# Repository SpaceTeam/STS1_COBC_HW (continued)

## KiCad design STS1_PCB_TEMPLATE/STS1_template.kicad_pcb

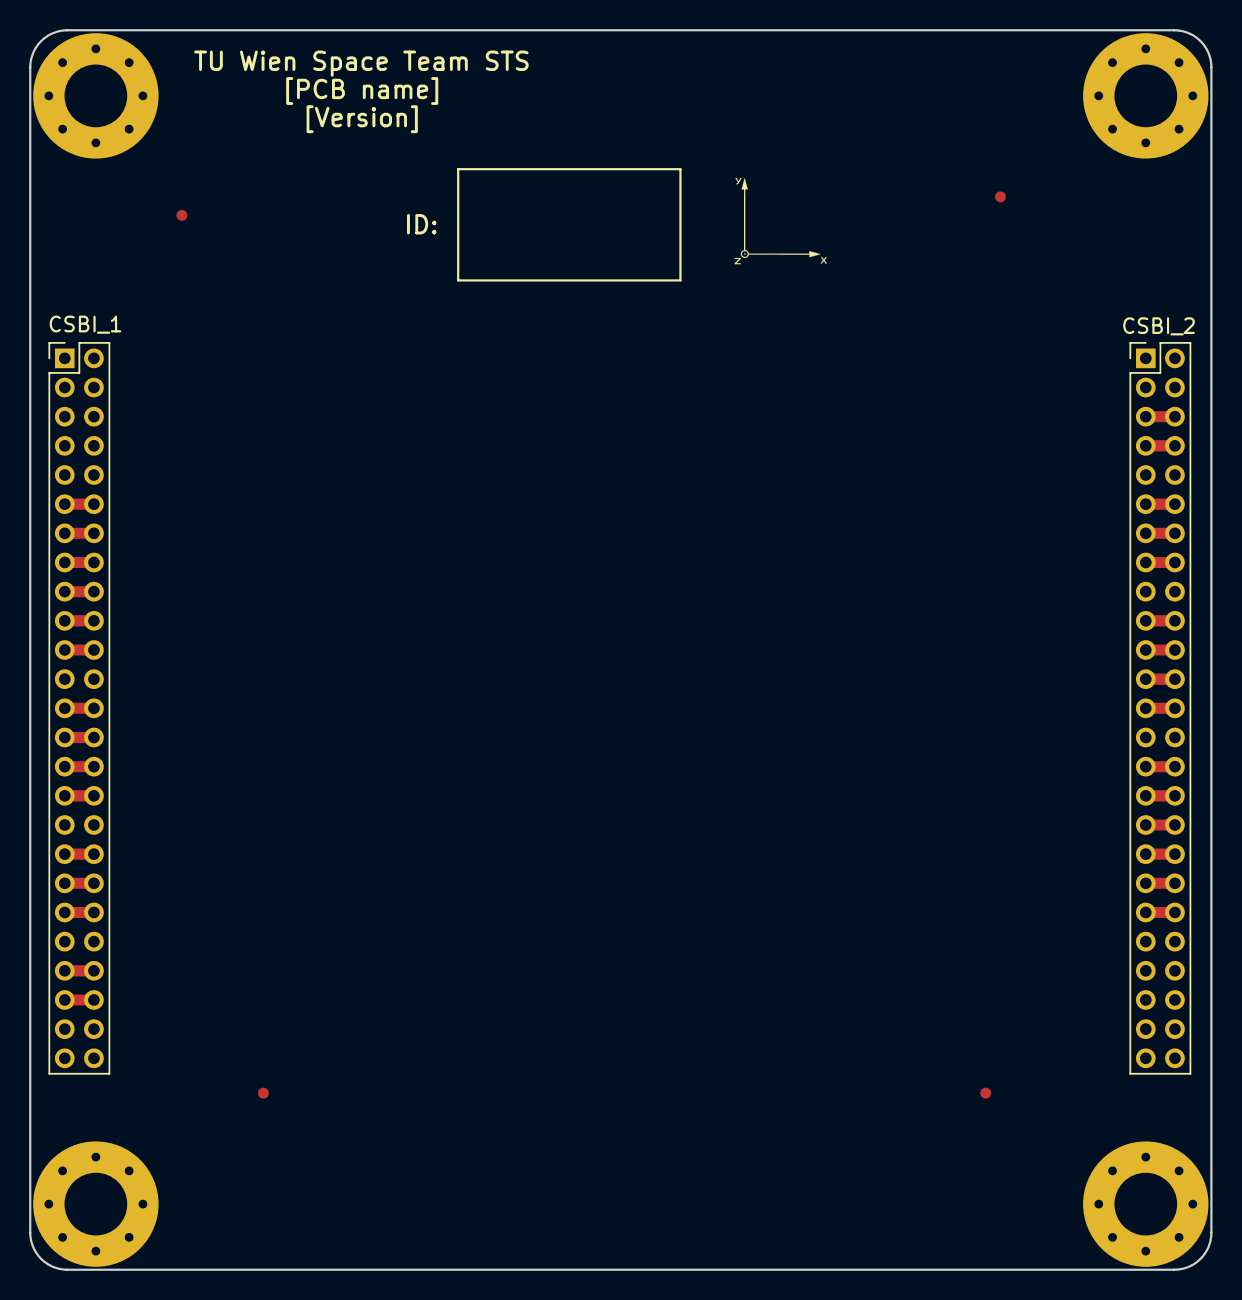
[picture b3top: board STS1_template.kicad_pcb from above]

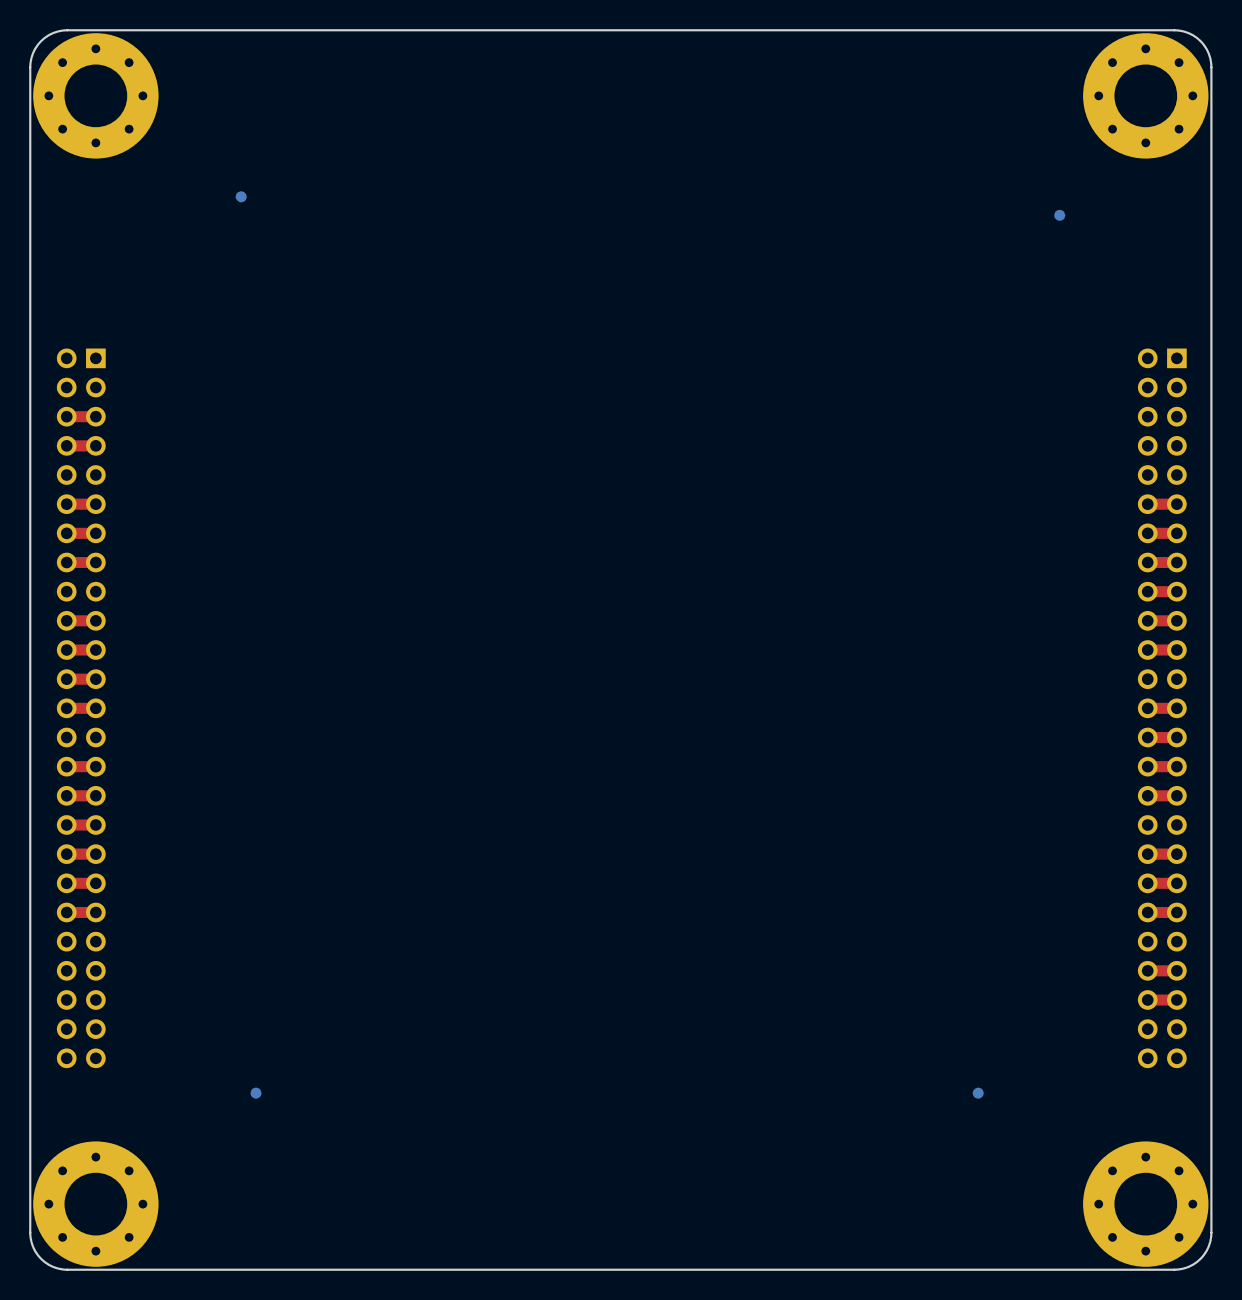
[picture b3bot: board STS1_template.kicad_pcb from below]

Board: 4 copper layers, 81.0 x 85.0 mm, 15 parts (4 on the bottom side), 32 nets.

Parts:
CSBI_1, CSBI_2: Conn_02x25_Odd_Even; PinHeader_2x25_P2.00mm_Vertical
FID1, FID2, FID3, FID4, FID5, FID6, FID7, FID8: Fiducial; Fiducial_0.75mm_Mask1.5mm
H1, H2, H3, H4: MountingHole_Pad; MountingHole_4.3mm_M4_Pad_Via
U1: coordinate_system; Coordinates

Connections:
/STS1_connector/COBC_SPI_1: CSBI_2.29, CSBI_2.30
/STS1_connector/COBC_SPI_2: CSBI_2.31, CSBI_2.32
/STS1_connector/COBC_SPI_3: CSBI_2.33, CSBI_2.34
/STS1_connector/COBC_SPI_4: CSBI_2.35, CSBI_2.36
/STS1_connector/COBC_SPI_5: CSBI_2.37, CSBI_2.38
/STS1_connector/COBC_SPI_6: CSBI_2.39, CSBI_2.40
/STS1_connector/EDU_BOOT: CSBI_2.15, CSBI_2.16
/STS1_connector/EDU_EN: CSBI_1.39, CSBI_1.40
/STS1_connector/EDU_Heartbeat: CSBI_1.35, CSBI_1.36
/STS1_connector/EDU_SPI_1: CSBI_1.21, CSBI_1.22
/STS1_connector/EDU_SPI_2: CSBI_1.19, CSBI_1.20
/STS1_connector/EDU_SPI_3: CSBI_1.17, CSBI_1.18
/STS1_connector/EDU_SPI_4: CSBI_1.15, CSBI_1.16
/STS1_connector/EDU_SPI_5: CSBI_1.13, CSBI_1.14
/STS1_connector/EDU_SPI_6: CSBI_1.11, CSBI_1.12
/STS1_connector/EDU_UPDATE: CSBI_1.37, CSBI_1.38
/STS1_connector/EPS_ANT_DEPLOYED: CSBI_2.23, CSBI_2.24
/STS1_connector/EPS_BAT_GOOD: CSBI_2.21, CSBI_2.22
/STS1_connector/EPS_CHARGING: CSBI_2.25, CSBI_2.26
/STS1_connector/UART_COBC_EDU_1: CSBI_1.45, CSBI_1.46
/STS1_connector/UART_COBC_EDU_2: CSBI_1.43, CSBI_1.44
/STS1_connector/UCI_COBC_3V3: CSBI_2.19, CSBI_2.20
/STS1_connector/UCI_COBC_UART_1: CSBI_2.5, CSBI_2.6
/STS1_connector/UCI_COBC_UART_2: CSBI_2.7, CSBI_2.8
GND: CSBI_1.1, CSBI_1.2, CSBI_1.3, CSBI_1.4, CSBI_1.9, CSBI_1.10, CSBI_1.23, CSBI_1.24, CSBI_1.33, CSBI_1.34, CSBI_1.41, CSBI_1.42, CSBI_1.47, CSBI_1.48, CSBI_1.49, CSBI_1.50, CSBI_2.1, CSBI_2.2, CSBI_2.3, CSBI_2.4, CSBI_2.9, CSBI_2.10, CSBI_2.17, CSBI_2.18, CSBI_2.27, CSBI_2.28, CSBI_2.41, CSBI_2.42, CSBI_2.47, CSBI_2.48, CSBI_2.49, CSBI_2.50, H1.1, H2.1, H3.1, H4.1
unnamed: CSBI_1.25, CSBI_1.26
unnamed: CSBI_1.27, CSBI_1.28
unnamed: CSBI_1.29, CSBI_1.30
unnamed: CSBI_1.31, CSBI_1.32
unnamed: CSBI_2.11, CSBI_2.12
unnamed: CSBI_2.13, CSBI_2.14
VBUS: CSBI_1.5, CSBI_1.6, CSBI_1.7, CSBI_1.8, CSBI_2.43, CSBI_2.44, CSBI_2.45, CSBI_2.46

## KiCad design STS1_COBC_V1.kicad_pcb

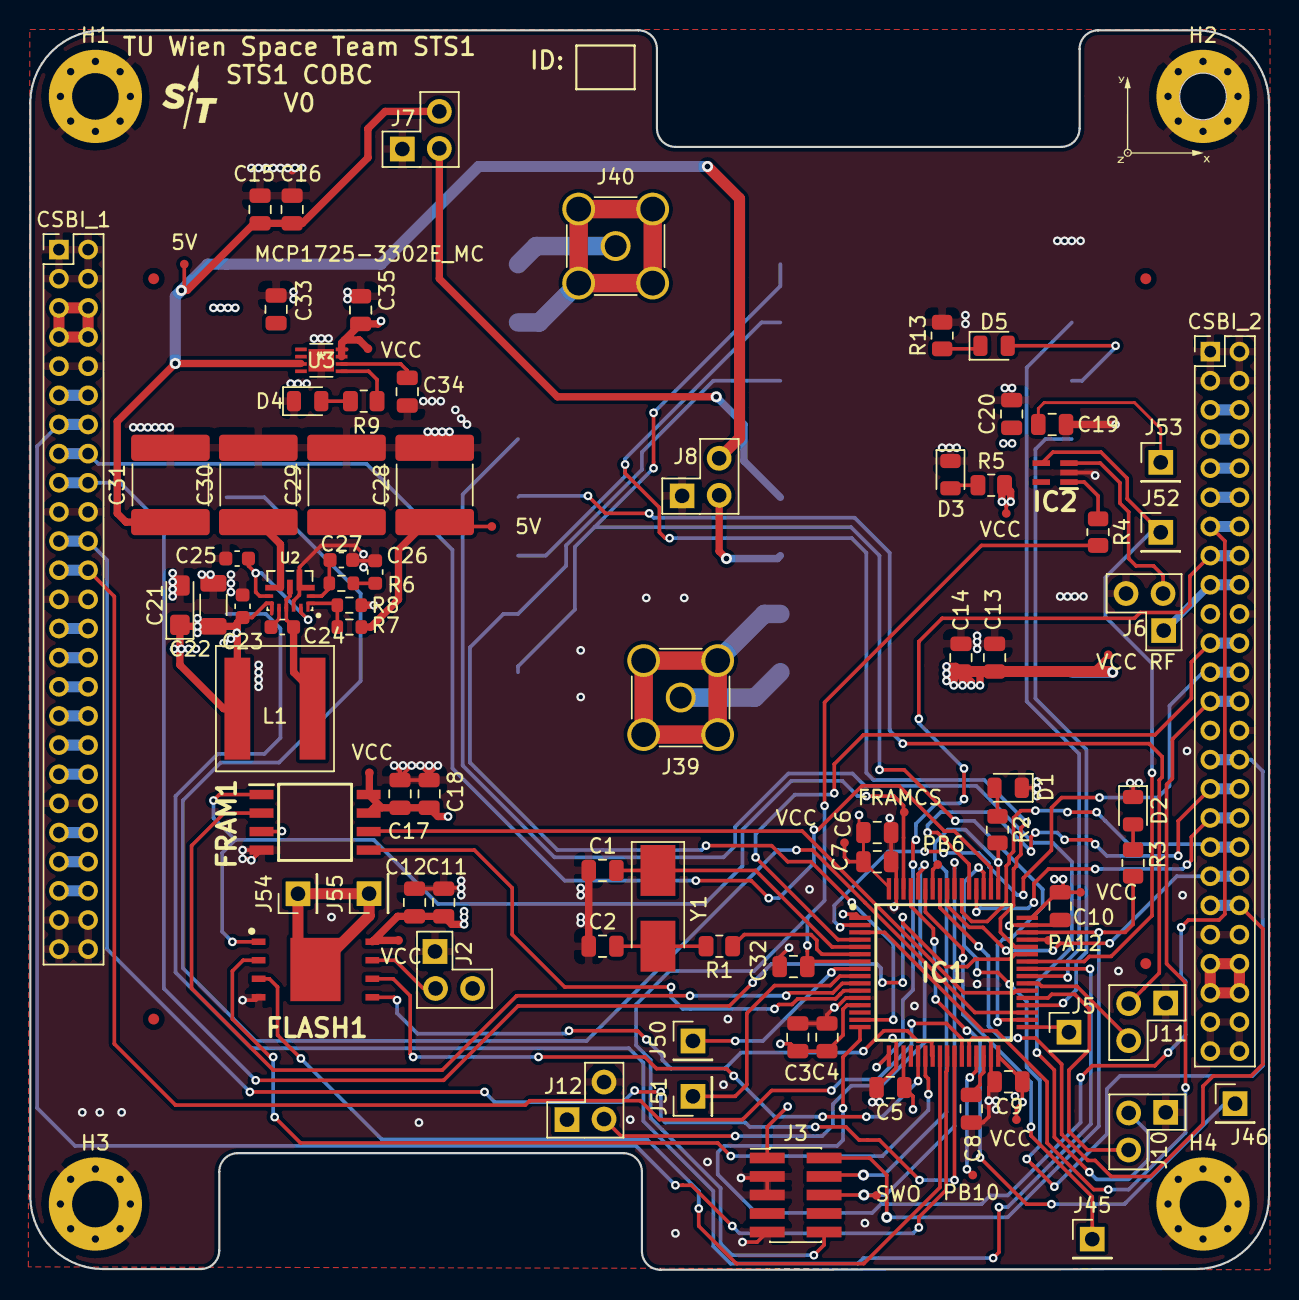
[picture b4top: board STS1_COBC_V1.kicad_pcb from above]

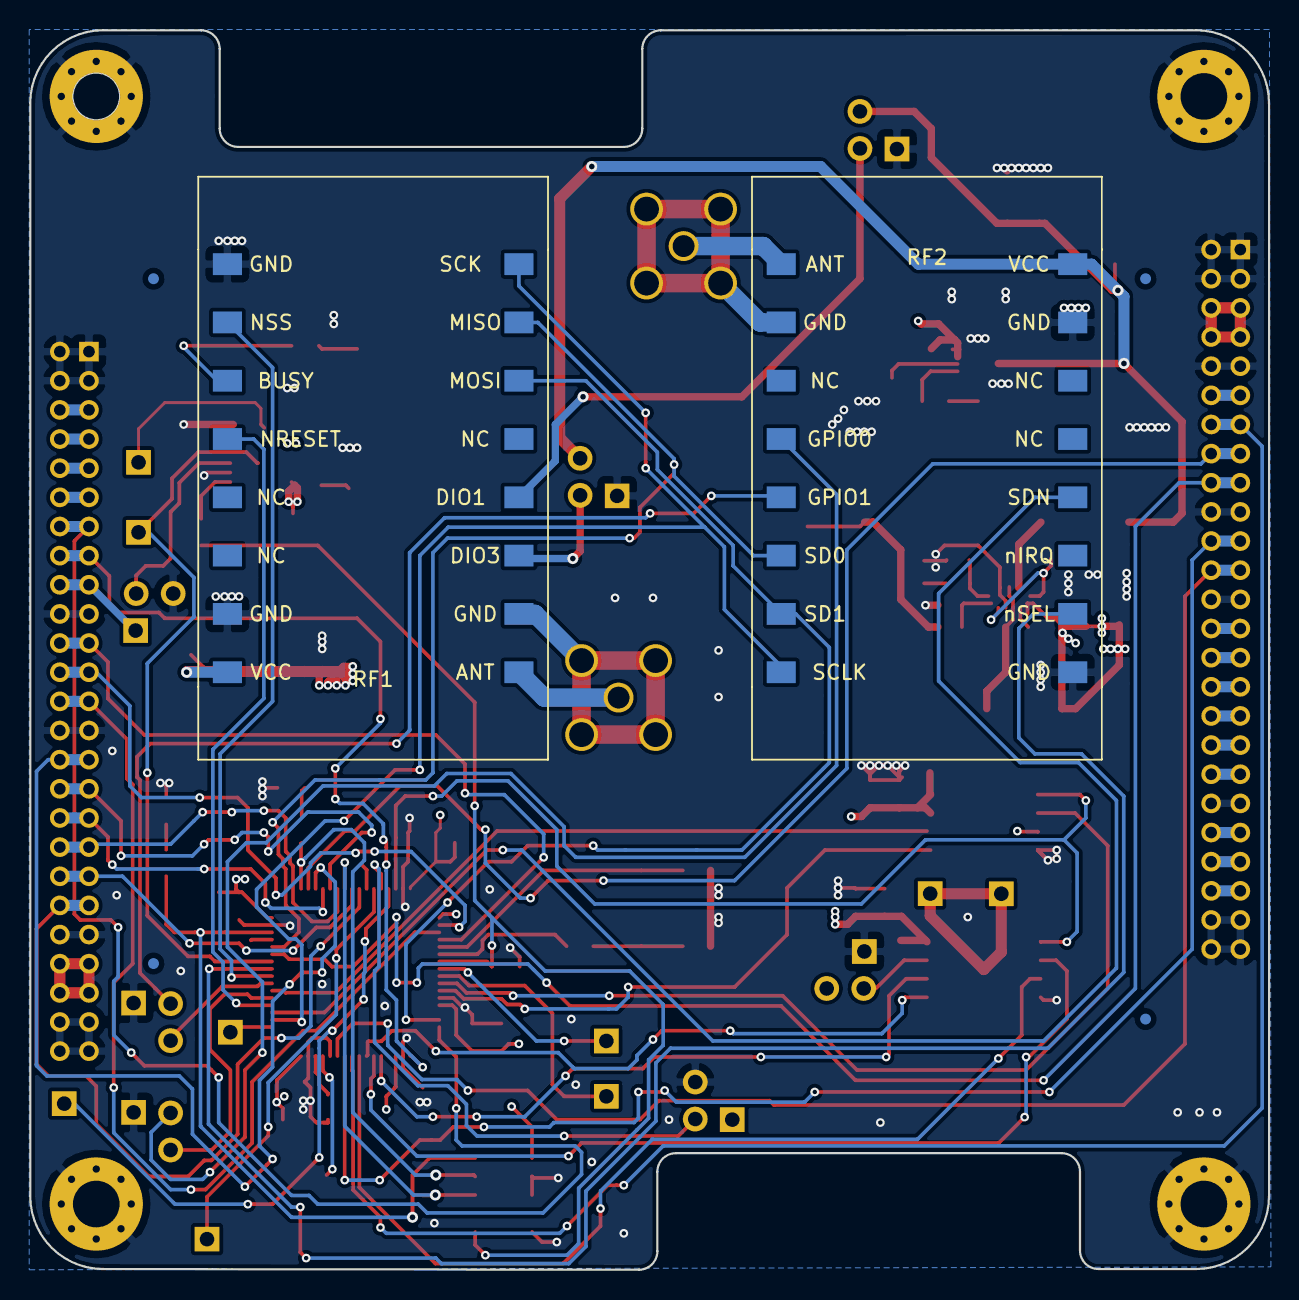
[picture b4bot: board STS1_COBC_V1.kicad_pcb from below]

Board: 4 copper layers, 85.0 x 85.0 mm, 109 parts (6 on the bottom side), 95 nets.

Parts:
5V, 5V#2: TestPoint; STS1_Testpoint
C1, C2: 20p; C_0805_2012Metric
C3: 1u; C_0805_2012Metric
C4, C5, C7, C9, C10, C11, C13, C15, C17, C19, C32: 100n; C_0805_2012Metric
C6, C8: 4.7u; C_0805_2012Metric
C12, C14, C16, C18, C20: 47u; C_0805_2012Metric
C21: 47uF; CP_EIA-3216-18_Kemet-A
C22: 10uF; C_1206_3216Metric
C23: 100nF; C_0603_1608Metric
C24: 150nF; C_0603_1608Metric
C25: 2.2uF; C_0603_1608Metric
C26: 39nF; C_0603_1608Metric
C27: 82pF; C_0603_1608Metric
C28, C29, C30, C31: 68uF; C_2220_5650Metric
C33, C35: 4.7µF; C_0805_2012Metric
C34: 0.1µ; C_0805_2012Metric
CSBI_1, CSBI_2: Conn_02x25_Odd_Even; PinHeader_2x25_P2.00mm_Vertical
D1, D2, D3, D4, D5: LED; LED_0805_2012Metric
FID1, FID2, FID3, FID4, FID5, FID6, FID7, FID8: Fiducial; Fiducial_0.75mm_Mask1.5mm
FLASH1: W25Q01JVZEIQ; SON127P800X600X80-9N-D
FRAM1: CY15B108QN-40SXI; SOIC127P800X203-8N
FRAMCS: TestPoint; STS1_Testpoint
H1, H2, H3, H4: MountingHole_Pad; MountingHole_3.2mm_M3_Pad_Via
IC1: STM32F411RET6TR; QFP50P1200X1200X160-64N
IC2: STWD100PYW83F; SOT65P210X110-5N
J2, J6, J7, J8, J10, J11, J12: Conn_01x03_Male; PinHeader_1x03_P2.54mm_Vertical_umdieEcke
J3: Conn_ARM_JTAG_SWD_10; PinHeader_2x05_P1.27mm_Vertical_SMD
J5, J45, J46, J50, J51, J52, J53, J54: Conn_01x01_Male; PinHeader_1x01_P2.54mm_Vertical
J39, J40: Conn_Coaxial; SMA_Amphenol_901-144_Vertical
J55: Conn_01x01_Female; PinHeader_1x01_P2.54mm_Vertical
L1: 1uH; XAL8080
PA12: TestPoint; STS1_Testpoint
PB6, PB10: TestPoint; STS1_Testpoint
R1: 220; R_0805_2012Metric
R2, R3, R5: 100; R_0805_2012Metric
R4: 4k7; R_0805_2012Metric
R6, R8: 48k7; R_0603_1608Metric
R7: 357k; R_0603_1608Metric
R9: 1k; R_0805_2012Metric
R13: 15; R_0805_2012Metric
RF1: LoRa1268F30
RF2: RF4463F30; STS1_RF4463F30
SWO: TestPoint; STS1_Testpoint
U1: coordinate_system; Coordinates
U2: TPS61288; VQFN-HR
U3: MCP1725-3302E_MC; MCP1725-3302E&slash_MC
VCC: TestPoint; STS1_Testpoint
VCC RF: TestPoint; STS1_Testpoint
VCC#2, VCC#3, VCC#4, VCC#5, VCC#6, VCC#7: TestPoint; STS1_Testpoint
Y1: 12MHz; Crystal_SMD_5032-2Pin_5.0x3.2mm_HandSoldering

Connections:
+3V3: C3.1, C4.2, C5.2, C6.2, C7.2, C9.1, C10.1, C11.2, C12.2, C17.2, C18.2, C19.1, C20.1, C35.2, CSBI_2.17, CSBI_2.18, FLASH1.8, FRAM1.3, FRAM1.7, FRAM1.8, IC1.1, IC1.13, IC1.19, IC1.32, IC1.48, IC1.64, IC2.5, J2.3, J3.1, J6.1, J12.1, J53.1, R5.2, U3.7, U3.8, VCC.1, VCC#2.1, VCC#3.1, VCC#4.1, VCC#5.1, VCC#6.1, VCC#7.1
+5V: 5V.1, 5V#2.1, C13.1, C14.1, C15.1, C16.1, C28.1, C29.1, C30.1, C31.1, C33.2, J7.3, J8.3, R7.1, RF1.1, RF2.1, U2.5, U3.1, U3.2, U3.3, VCC RF.1
/COBC_SPI_1: CSBI_2.29, CSBI_2.30, IC1.51
/COBC_SPI_2: CSBI_2.31, CSBI_2.32, IC1.53
/COBC_SPI_3: CSBI_2.33, CSBI_2.34, IC1.52
/COBC_SPI_4: CSBI_2.35, CSBI_2.36, IC1.54
/COBC_SPI_5: CSBI_2.37, CSBI_2.38, IC1.56
/COBC_SPI_6: CSBI_2.39, CSBI_2.40, IC1.57
/EDU_EN: CSBI_1.21, CSBI_1.22, IC1.26
/EDU_Heartbeat: CSBI_1.13, CSBI_1.14, IC1.25
/EDU_UPDATE: CSBI_1.23, CSBI_1.24, IC1.27
/EPS_ANT_DEP: CSBI_2.23, CSBI_2.24, IC1.2
/EPS_BAT_GOOD: CSBI_2.21, CSBI_2.22, IC1.4
/EPS_CHARGING: CSBI_2.25, CSBI_2.26, IC1.3
/LoRa_NRESET: IC1.36, RF1.5
/RF4463F30_GPIO0: IC1.37, J10.3
/RF4463F30_GPIO1: IC1.39, J11.3
/RF4463F30_SDN: IC1.35, RF2.5
/STS1_COBC_Memories/FRAM_CLK: FRAM1.6, IC1.38
/STS1_COBC_Memories/FRAM_CS: FLASH1.1, FRAM1.1, FRAMCS.1, IC1.62
/STS1_COBC_Memories/FRAM_DataInput: FRAM1.5, IC1.11
/STS1_COBC_Memories/FRAM_DataOutput: FRAM1.2, IC1.10
/STS1_COBC_Memories/Flash_CLK: FLASH1.6, IC1.21
/STS1_COBC_Memories/Flash_DataInput: FLASH1.5, IC1.23
/STS1_COBC_Memories/Flash_DataOutput: FLASH1.2, IC1.22
/STS1_COBC_Memories/Flash_WP: FLASH1.3, IC1.24
/STS1_COBC_uC/PB6: IC1.58, PB6.1
/STS1_COBC_uC/PB7: IC1.59, J45.1
/STS1_COBC_uC/PB9: IC1.61, J46.1
/STS1_COBC_uC/PC0: IC1.8, J50.1
/STS1_COBC_uC/PC1: IC1.9, J51.1
/STS1_COBC_uC/SPI4_NSS: IC1.33, J5.1
/STS1_COBC_uC/STM32_NRST: C32.2, IC1.7, J3.10, R4.2
/STS1_COBC_uC/SWDCLK: IC1.49, J3.4, R2.2
/STS1_COBC_uC/SWDIO: IC1.46, J3.2, R3.2
/STS1_COBC_uC/SWO: IC1.55, J3.6, SWO.1
/STS1_COBC_uC/WDT_Clear: IC1.42, IC2.4, J52.1
/STS1_Connector/EDU_SPI_1: CSBI_1.27, CSBI_1.28
/STS1_Connector/EDU_SPI_2: CSBI_1.29, CSBI_1.30
/STS1_Connector/EDU_SPI_3: CSBI_1.31, CSBI_1.32
/STS1_Connector/EDU_SPI_4: CSBI_1.33, CSBI_1.34
/STS1_Connector/EDU_SPI_5: CSBI_1.35, CSBI_1.36
/STS1_Connector/EDU_SPI_6: CSBI_1.37, CSBI_1.38
/STS1_RF/LoRa_MISO: IC1.44, RF1.10, RF2.11
/STS1_RF/LoRa_MOSI: IC1.15, RF1.11, RF2.10
/STS1_RF/LoRa_NSS: IC1.40, RF1.7
/STS1_RF/LoRa_SMA_GND: J39.2, RF1.15
/STS1_RF/LoRa_SPI_CLK: IC1.34, RF1.9, RF2.9
/STS1_RF/RF4463_ANT_GND: J40.2, RF2.15
/STS1_RF/RF4463_nSEL: IC1.41, RF2.7
/UART_COBC_EDU_1: CSBI_1.15, CSBI_1.16, IC1.50
/UART_COBC_EDU_2: CSBI_1.17, CSBI_1.18, IC1.43
/UCI_COBC_UART_1: CSBI_2.13, CSBI_2.14, IC1.16
/UCI_COBC_UART_2: CSBI_2.15, CSBI_2.16, IC1.17
GND: C1.1, C2.1, C3.2, C4.1, C5.1, C6.1, C7.1, C8.2, C9.2, C10.2, C11.1, C12.1, C13.2, C14.2, C15.2, C16.2, C17.1, C18.1, C19.2, C20.2, C21.2, C22.2, C23.2, C25.2, C26.2, C27.2, C28.2, C29.2, C30.2, C31.2, C32.1, C33.1, C34.2, C35.1, CSBI_1.1, CSBI_1.2, CSBI_1.3, CSBI_1.4, CSBI_1.9, CSBI_1.10, CSBI_1.19, CSBI_1.20, CSBI_1.25, CSBI_1.26, CSBI_1.39, CSBI_1.40, CSBI_1.47, CSBI_1.48, CSBI_1.49, CSBI_1.50, CSBI_2.1, CSBI_2.2, CSBI_2.3, CSBI_2.4, CSBI_2.19, CSBI_2.20, CSBI_2.27, CSBI_2.28, CSBI_2.41, CSBI_2.42, CSBI_2.47, CSBI_2.48, CSBI_2.49, CSBI_2.50, D1.1, D2.1, D3.1, D4.1, FLASH1.4, FRAM1.4, H1.1, H2.1, H3.1, H4.1, IC1.12, IC1.18, IC1.28, IC1.31, IC1.47, IC1.63, IC2.2, J2.1, J3.3, J3.5, J3.9, J6.3, J7.1, J8.1, J10.1, J11.1, J12.3, R8.2, R13.2, RF1.2, RF1.8, RF2.2, RF2.8, U2.3, U2.10, U3.4, U3.9
unnamed: C1.2, IC1.5, Y1.1
unnamed: C2.2, R1.2, Y1.2
unnamed: C8.1, IC1.30
unnamed: C24.1, U2.8
unnamed: C24.2, L1.2, U2.4, U2.9
unnamed: C25.1, U2.6, U2.11
unnamed: C26.1, R6.2
unnamed: C27.1, R6.1, U2.2
unnamed: C34.1, U3.6
unnamed: CSBI_1.11, CSBI_1.12
unnamed: CSBI_1.41, CSBI_1.42
unnamed: CSBI_1.43, CSBI_1.44
unnamed: CSBI_1.45, CSBI_1.46
unnamed: CSBI_2.5, CSBI_2.6
unnamed: CSBI_2.7, CSBI_2.8
unnamed: CSBI_2.9, CSBI_2.10
unnamed: CSBI_2.11, CSBI_2.12
unnamed: D1.2, R2.1
unnamed: D2.2, R3.1
unnamed: D3.2, R5.1
unnamed: D4.2, R9.2
unnamed: D5.1, R13.1
unnamed: D5.2, RF1.6
unnamed: FLASH1.7, J2.2
unnamed: FLASH1.9, J54.1, J55.1
unnamed: IC1.6, R1.1
unnamed: IC1.29, PB10.1
unnamed: IC1.45, PA12.1
unnamed: IC1.60, J12.2
unnamed: IC2.1, R4.1
unnamed: IC2.3, J6.2
unnamed: J7.2, RF1.13
unnamed: J8.2, RF1.14
unnamed: J10.2, RF2.13
unnamed: J11.2, RF2.12
unnamed: J39.1, RF1.16
unnamed: J40.1, RF2.16
unnamed: R7.2, R8.1, U2.1
unnamed: R9.1, U3.5
VBUS: C21.1, C22.1, C23.1, CSBI_1.5, CSBI_1.6, CSBI_1.7, CSBI_1.8, CSBI_2.43, CSBI_2.44, CSBI_2.45, CSBI_2.46, L1.1, U2.7

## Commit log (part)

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2021-08-10 first prototype cobc
    STM32F411RE, Flash and Fram added
2021-08-10 Removed subrepo
2021-08-10 Added template
2021-08-17 Struggle with repo and gitkraken
2021-08-23 added Leds and few pin headers
2021-08-25 schematic cleanup
2021-08-30 RF modules added + some tweaking on STM32
2021-09-14 finished schematic
2021-09-15 new template
2021-10-09 BuckBoost added
2021-10-12 schematic done
    final tweaks (adding LEDS, pin headers, moving circuits...)
2021-10-19 Correct path to samac_sys lib in schematics
    Fix #1
2021-10-19 Add basic schematic for 5V DCDC
2021-10-19 Select parts for dcdc converter
2021-10-19 Update dcdc footprint
2021-10-19 Add reference layout for dcdc
2021-10-19 Change soldermask settings for smaller ics
2021-11-03 Issues removed + further layout development
2021-11-06 component layout finished -> now wiring
2021-11-30 final version1
2021-12-01 added powerplane + testpoints + some debugging
2021-12-05 finished prototype
2021-12-13 COBC v1 (ordered)
2021-12-13 renamed files
2021-12-17 Version 1
    Version 1 of the PCBs of the COBC, ordered in 2021.12
2022-06-26 Work in progress v2
    Quick push for Raphael
2022-06-26 deleting folder content v1
2022-06-26 v2 copied into the v1 folder
2022-07-03 more work done
    All parts besides RF added
2022-07-15 Cleanup
2022-07-16 add RF part
2022-08-03 ordered version cobc v2
2022-09-13 add values for si4463 input matching network
2023-01-06 Removed submodule lsf-kicad-lib
2023-01-06 Remove old submodules
2023-01-06 Update pcb libraries
2023-02-03 V2.5
2023-03-21 Set all passive components (except in the RF path) to 0603
2023-03-21 Add missing C79 capacitor
2023-05-01 Add resetdog timer (RDT) schematics
2023-05-01 Add temporarily KiCad files to .gitignore
2023-05-07 Add preliminary resetdog PCB layout.
2023-05-07 Change version on schematics/pcb to v2.6
2023-05-08 Rotate coordinate system (x,y,z)->(y,-x,z)
2023-05-08 Modify resetdog
2023-05-08 Add missing VBUS connection
2023-05-08 Replace schematics symbol of D9 and D10 diods
2023-05-10 Flip D10 to correct orientation
2023-05-29 Remove V1 files and rename V2 files
2023-05-30 feat: Remove all useless files
2023-05-30 feat: remove useless bak files
2023-05-30 feat: remove duplicates
2023-05-30 feat: add lsf-kicad libs again
2023-05-30 feat: remove old BOM export
2023-05-30 feat: clean up schematic
2023-05-30 feat: update RF hardware and clean up ERC errors
2023-05-30 feat: more schematic cleanup
2023-05-30 feat: layout changed for new RF part
2023-05-30 feat: clean up old kicad 5 files
2023-05-31 feat: update pcb libs
2023-05-31 feat: change default 3d export path
2023-06-06 feat(RF): better LPF tuning and add part numbers to all inductors
2023-06-08 Add missing 3D models and fix 3D model path issues
2023-06-08 Fix labels
2023-06-10 Refill and add Gerber to .gitingore
2023-06-10 Fix path for 3D model of STWD100 wathdog IC
2023-06-22 Fix footprint assignments: all IC should have U designator
2023-06-22 Fix footprint assignments: all CSBI headers should have J designator
2023-06-22 Exclude jumpers, mounting holes, fiducials etc. from BOM
2023-06-22 Change version 2.6->3.0
2023-06-22 Fix mismatch between footprint and part number for C48, C72, C74, R13, R24, R21, R27, R28, R30, R31
2023-07-08 Update values of components in the RF subsystem and swap CL instead of LC filter (L14 and C67)
2023-11-01 Reorganize and clean-up the components around the STM. Pinout changes: 1) Flash_CS moved from PB9 to PA4 2) Dosi_En added on PB10 3) EDU_Boot_Pin added on PB2 4) WDT_Clear moved from PA9 to PB9
2023-11-02 Reorganize silkscreen labels
2023-11-08 Create LICENSE
2023-11-13 Added 3D models for some components: SMB connector, D1 diode and oscillators
2023-11-21 Added untracked step files
2024-03-03 Make changes to the RDT: switch off AR, add Schmidt trigger for MR, change values of R40 and C83
2024-03-03 Change version to 2.7
2024-03-16 Add latchup protection circuits
2024-03-16 Add microcontroller supervisory circuit
2024-03-16 Add a temperature sensor near RF amplifier chip
2024-03-16 Add a delay capacitor to keep DC-DC turned off for some time after ~EN pin is toggled
2024-03-16 Add for new lines to the UCI bus; plus minor fixes: introduce resistor in EDU_BOOT_Pin line, remove zener before DC-DC ~EN input
2024-03-16 Change U28 OR gate to AND gate
2024-03-16 Add 3D models for AND gate and FRAM
2024-03-17 Include R14, C95, R15 and Q2 into the bill of materials
2024-03-17 Relocate Q8 mosfet to protect the DC-DC from UCI_COBC_5V input and make 5V traces thicker
2024-03-17 Move DC-DC circuit 2cm down and reposition latch-up circuits
2024-03-17 Make slight cleanup
2024-03-20 Change FRAM to the one recommended by Infineon: CY15B108QN-40SXI -> CY15B104Q-SXI
2024-03-24 Increase minimum via hole size from 0.2 mm to 0.3 mm
2024-06-16 Change version: 2.7 -> 3.0
2024-06-22 Add manufacture number and JLCPCB part number to components
2024-06-22 Exclude testpoints from bill of materials
2024-06-23 Remove Q8 and add zener diodes to protect output of LDOs and latch-up protection circuits
2024-06-23 Change symbol for U20 Schmitt trigger
2024-06-23 Add slew-rate control capacitors to latch-up protection circuits
2024-06-23 Add silkscreen labels near connectors
2024-06-23 Change coordinate system
2024-06-23 Update C67 part number
2024-06-24 Fix the issue with WDT intervening the programming cycle: use pins 7 and 9 of JTAG connector to pull ~EN pin of WDT to the high level
2024-07-01 Add a defined state (pulled to GND) of the output of LT1336 for the case when it is a shutdown state
2024-07-04 Add some redundancy to trigger the RTD: two STM pins should come high for the trigger event to happen
2024-07-05 Add some redundancy when the latch-up protection of the RF part is disabled: out of two STM pins, at least one should be high
2024-07-06 Add a 3D model of the 74LVC1G32GV_125 chip
2024-07-06 Decouple U29 from the ~RST comming from the JTAG connector
2024-07-06 Add a pull down resistor to RF_LATCHUP_DIS input
2024-07-06 Increase inrush current threshold for latch-up protection: C87, C91 22 pF -> 100 nF
2024-07-06 Make a jump-start pulse for RTD shorter: R40 22 kOhm -> 10 kOhm, C83 10 uF -> 47 nF
2024-07-07 Adhere to the recommendations from AD589 datasheet: R42, R80 27k -> 6.8k for ~500 uA current and add 1 nF shunt capacitor
2024-07-07 Remove disable RTD jumper
2024-07-07 Do not populate R69, R70 and R71 on the flight model CSBI-JTAG interface won't be used
2024-07-07 Update the 12 MHz crystal oscillator value and change the related capacitors: C13, C14 20 pF -> 13 pF
2024-07-07 Add a couple of Zener diodes to protect inputs of MOSFETs
2024-07-12 Fix power domain crossing issue between RF and STM units
2024-07-13 Fix power domain crossing issue between COBC and EPS
2024-07-13 Increase latch-up protection recovery time from ~10 ms to ~100 ms and add some GND vias to connect disconnected parts for In1.Cu layer
2024-07-13 Increase delay before RTD toggles the DC-DC converter on and off: C95 47 nF -> 4.7 uF
2024-07-13 Add series resistors to the outputs of STM
2024-07-14 Add more series resistors to the outputs of STM and move labels near CSBI to the side of the PCB
2024-07-15 Switch RTD MC14541BD IC from single cycle mode to recycle mode, but leave an option to switch back
2024-07-23 Update the manufacturer part number for some of components to be compatible with avaiable parts in the JLC parts database
2024-07-23 Refill zones
2024-07-25 Exclude R11 (DNP) from position file
2024-07-28 Replace the U12 from FPF2702 to TPS22950-Q1: R30 is pulling down, R31: 110K -> 470 Ohm, U7 is removed, since ON is active high now
2024-07-28 Add a pull-up resistor for FLT pin of U12 and decouple U12 and STM with a series resistor
2024-07-28 Make stylistic changes to the schematics
2024-07-28 Replace U11 NL17SV04XV5T2G with 74LVC1G14Z-7 and add MFT number for R31
2024-07-28 Change MFT number for R31
2024-08-31 Fix bug with footprints of components for R27 and R28: 0402->0603, replace manufacter number and JLCPCB part id.
2024-08-31 Exclude R70 and R71 from BOM (they should not be populated on FM).
2024-09-05 Add a kicad project of an adapter from STlink to COBC.
2026-04-09 Fix the RF-STM SPI communication issue: reduce the value of R81 from 4.7K to 470 Ohm
2026-04-09 Tweak RF amplifier settings: C77 from 24pF to 33pF, L18 from 8.2nH to 5.6nH
2026-04-09 Increase the value of R54 from 220K to 1M to reduce the STM latch-up protection threshold to ~190 mA
2026-04-15 Change version v3.0 -> v3.1
2026-06-25 Update (automatic) paths to 3D models
